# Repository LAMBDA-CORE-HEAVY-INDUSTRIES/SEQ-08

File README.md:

# SEQ-08

Desktop STM32F411 sequencer with eight CV outputs, eight gate outputs, clock I/O, and reset input.

- [Hardware design](doc/hw.md)
- [Bill of materials](doc/bom.md)
- [KiCad projects](pcb/README.md)
- [Firmware](fw/README.md)

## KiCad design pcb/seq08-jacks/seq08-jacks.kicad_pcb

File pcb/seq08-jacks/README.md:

# SEQ-08 jack board

This passive panel PCB holds nineteen PJ398SM jacks:

- J1-J8: CV outputs
- J9-J16: gate outputs
- J17: clock input
- J18: clock output
- J19: reset input
- J24-J25: keyed IDC connections to the main board

The clock and reset normal contacts connect to ground. Other normal contacts remain unconnected.

The provisional board is 160 x 100 mm with four 3.2 mm M3 mounting holes. Confirm the enclosure geometry before routing or ordering it.

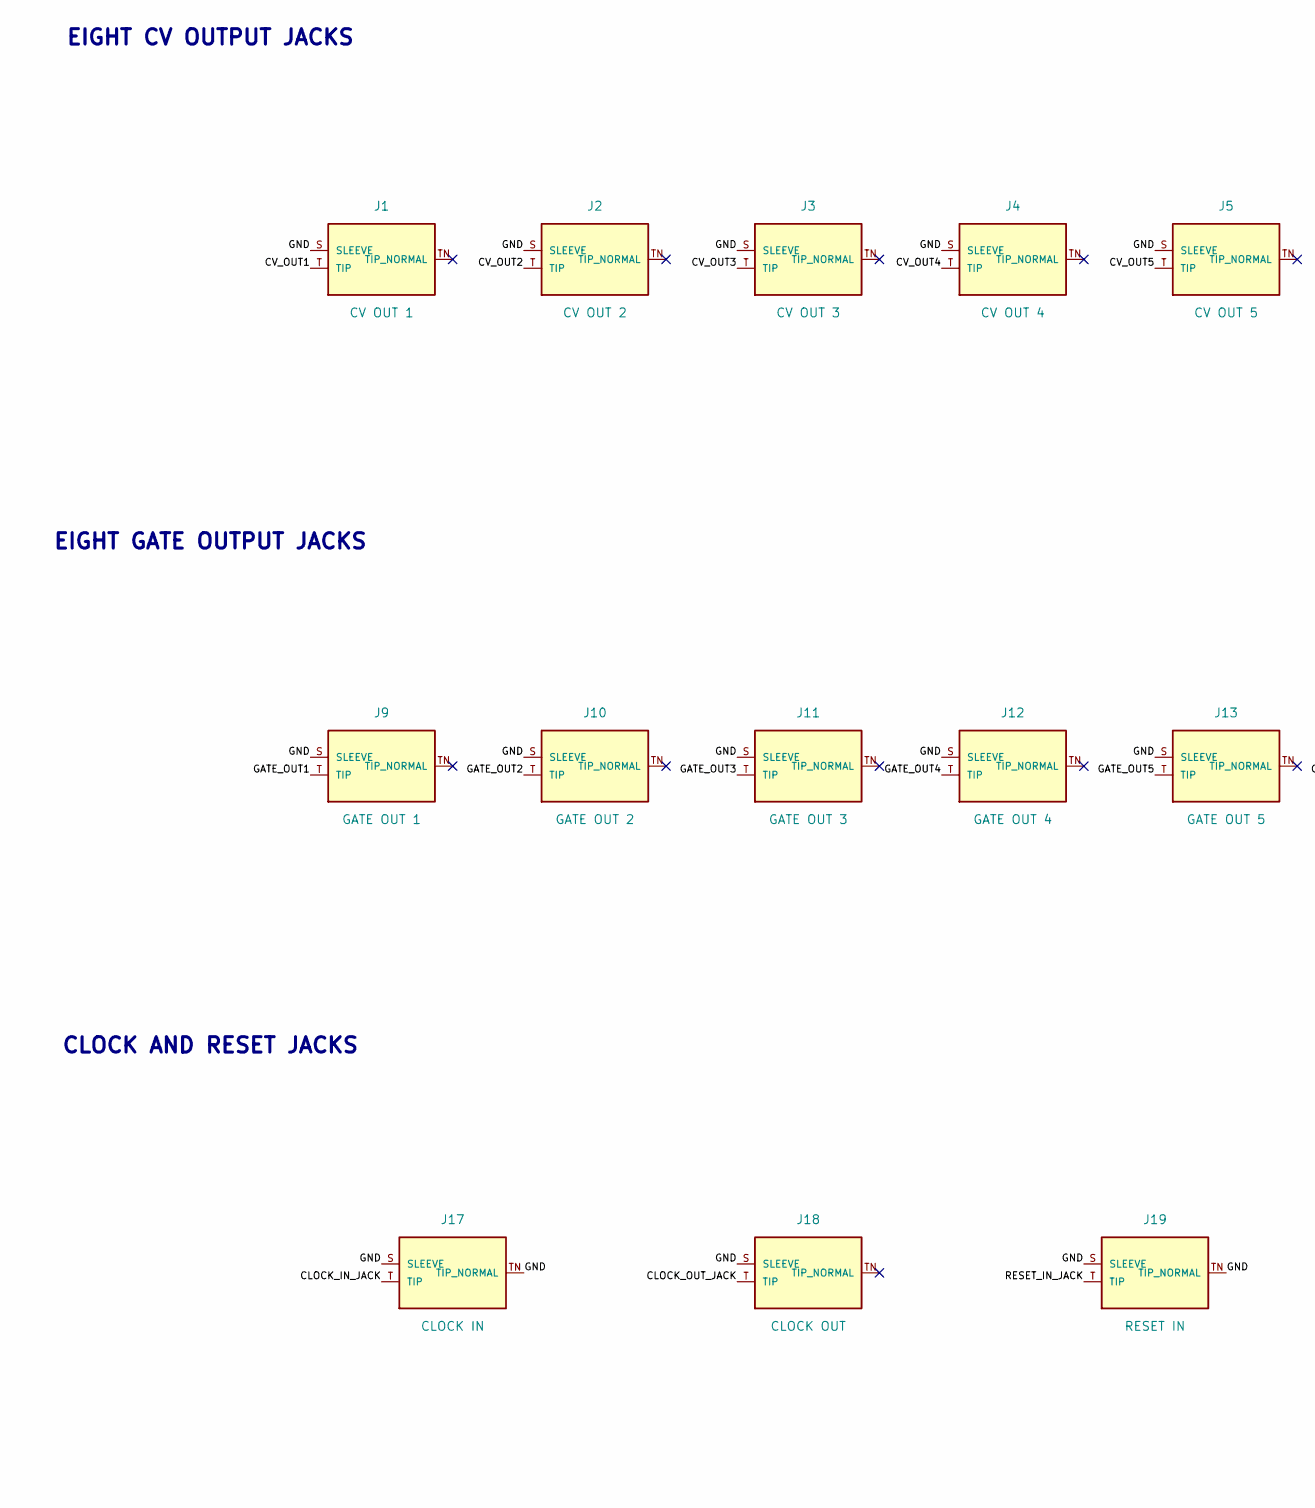
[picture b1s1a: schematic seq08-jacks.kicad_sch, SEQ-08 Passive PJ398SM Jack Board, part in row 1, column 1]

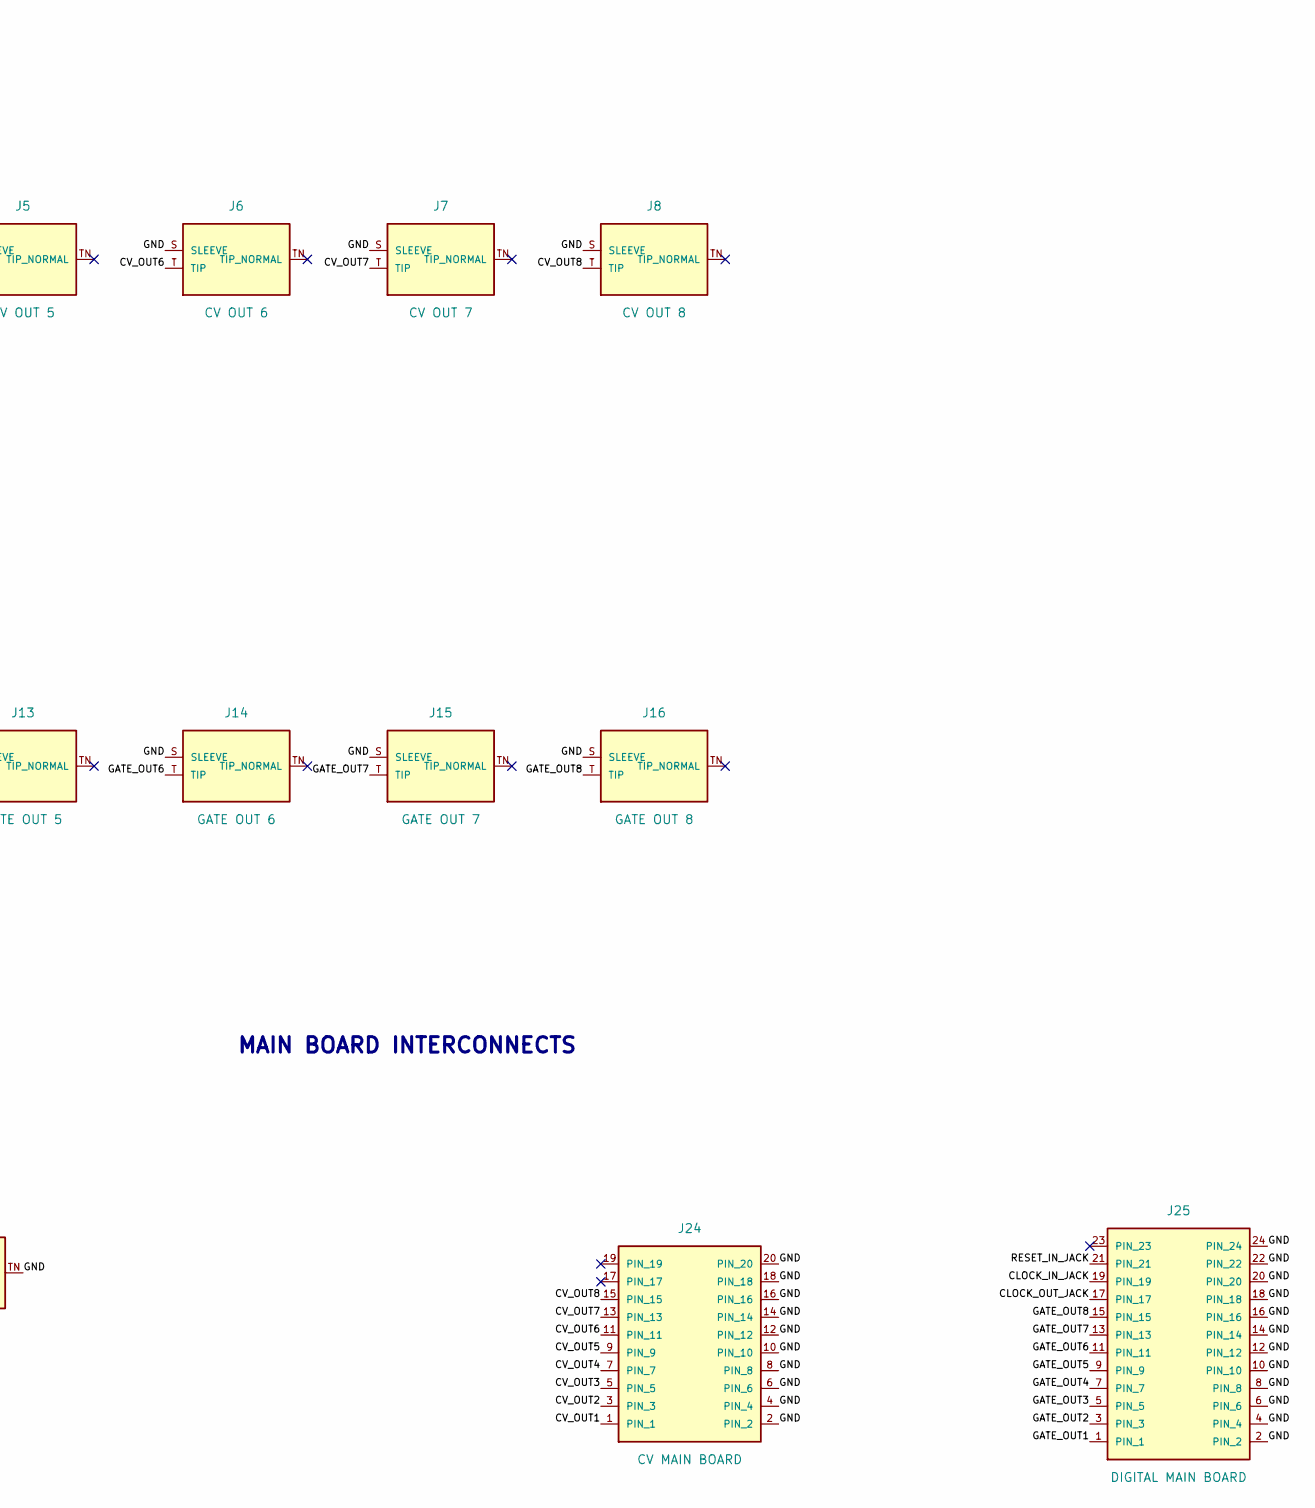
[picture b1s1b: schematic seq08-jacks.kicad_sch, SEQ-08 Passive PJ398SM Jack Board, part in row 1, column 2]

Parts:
J1: CV OUT 1; Jack_3.5mm_QingPu_WQP-PJ398SM_Vertical_CircularHoles
J2: CV OUT 2; Jack_3.5mm_QingPu_WQP-PJ398SM_Vertical_CircularHoles
J3: CV OUT 3; Jack_3.5mm_QingPu_WQP-PJ398SM_Vertical_CircularHoles
J4: CV OUT 4; Jack_3.5mm_QingPu_WQP-PJ398SM_Vertical_CircularHoles
J5: CV OUT 5; Jack_3.5mm_QingPu_WQP-PJ398SM_Vertical_CircularHoles
J6: CV OUT 6; Jack_3.5mm_QingPu_WQP-PJ398SM_Vertical_CircularHoles
J7: CV OUT 7; Jack_3.5mm_QingPu_WQP-PJ398SM_Vertical_CircularHoles
J8: CV OUT 8; Jack_3.5mm_QingPu_WQP-PJ398SM_Vertical_CircularHoles
J9: GATE OUT 1; Jack_3.5mm_QingPu_WQP-PJ398SM_Vertical_CircularHoles
J10: GATE OUT 2; Jack_3.5mm_QingPu_WQP-PJ398SM_Vertical_CircularHoles
J11: GATE OUT 3; Jack_3.5mm_QingPu_WQP-PJ398SM_Vertical_CircularHoles
J12: GATE OUT 4; Jack_3.5mm_QingPu_WQP-PJ398SM_Vertical_CircularHoles
J13: GATE OUT 5; Jack_3.5mm_QingPu_WQP-PJ398SM_Vertical_CircularHoles
J14: GATE OUT 6; Jack_3.5mm_QingPu_WQP-PJ398SM_Vertical_CircularHoles
J15: GATE OUT 7; Jack_3.5mm_QingPu_WQP-PJ398SM_Vertical_CircularHoles
J16: GATE OUT 8; Jack_3.5mm_QingPu_WQP-PJ398SM_Vertical_CircularHoles
J17: CLOCK IN; Jack_3.5mm_QingPu_WQP-PJ398SM_Vertical_CircularHoles
J18: CLOCK OUT; Jack_3.5mm_QingPu_WQP-PJ398SM_Vertical_CircularHoles
J19: RESET IN; Jack_3.5mm_QingPu_WQP-PJ398SM_Vertical_CircularHoles
J24: CV MAIN BOARD; IDC-Header_2x10_P2.54mm_Vertical
J25: DIGITAL MAIN BOARD; IDC-Header_2x12_P2.54mm_Vertical

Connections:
/CLOCK_IN_JACK: J17.T (TIP), J25.19 (PIN_19)
/CLOCK_OUT_JACK: J18.T (TIP), J25.17 (PIN_17)
/CV_OUT1: J1.T (TIP), J24.1 (PIN_1)
/CV_OUT2: J2.T (TIP), J24.3 (PIN_3)
/CV_OUT3: J3.T (TIP), J24.5 (PIN_5)
/CV_OUT4: J4.T (TIP), J24.7 (PIN_7)
/CV_OUT5: J5.T (TIP), J24.9 (PIN_9)
/CV_OUT6: J6.T (TIP), J24.11 (PIN_11)
/CV_OUT7: J7.T (TIP), J24.13 (PIN_13)
/CV_OUT8: J8.T (TIP), J24.15 (PIN_15)
/GATE_OUT1: J9.T (TIP), J25.1 (PIN_1)
/GATE_OUT2: J10.T (TIP), J25.3 (PIN_3)
/GATE_OUT3: J11.T (TIP), J25.5 (PIN_5)
/GATE_OUT4: J12.T (TIP), J25.7 (PIN_7)
/GATE_OUT5: J13.T (TIP), J25.9 (PIN_9)
/GATE_OUT6: J14.T (TIP), J25.11 (PIN_11)
/GATE_OUT7: J15.T (TIP), J25.13 (PIN_13)
/GATE_OUT8: J16.T (TIP), J25.15 (PIN_15)
/GND: J1.S (SLEEVE), J2.S (SLEEVE), J3.S (SLEEVE), J4.S (SLEEVE), J5.S (SLEEVE), J6.S (SLEEVE), J7.S (SLEEVE), J8.S (SLEEVE), J9.S (SLEEVE), J10.S (SLEEVE), J11.S (SLEEVE), J12.S (SLEEVE), J13.S (SLEEVE), J14.S (SLEEVE), J15.S (SLEEVE), J16.S (SLEEVE), J17.S (SLEEVE), J17.TN (TIP_NORMAL), J18.S (SLEEVE), J19.S (SLEEVE), J19.TN (TIP_NORMAL), J24.2 (PIN_2), J24.4 (PIN_4), J24.6 (PIN_6), J24.8 (PIN_8), J24.10 (PIN_10), J24.12 (PIN_12), J24.14 (PIN_14), J24.16 (PIN_16), J24.18 (PIN_18), J24.20 (PIN_20), J25.2 (PIN_2), J25.4 (PIN_4), J25.6 (PIN_6), J25.8 (PIN_8), J25.10 (PIN_10), J25.12 (PIN_12), J25.14 (PIN_14), J25.16 (PIN_16), J25.18 (PIN_18), J25.20 (PIN_20), J25.22 (PIN_22), J25.24 (PIN_24)
/RESET_IN_JACK: J19.T (TIP), J25.21 (PIN_21)

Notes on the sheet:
EIGHT CV OUTPUT JACKS
EIGHT GATE OUTPUT JACKS
CLOCK AND RESET JACKS
MAIN BOARD INTERCONNECTS

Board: 2 copper layers, 25 parts (0 on the bottom side), 20 nets, no tracks yet.

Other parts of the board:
H1, H2, H3, H4: M3 MOUNTING HOLE; MountingHole_3.2mm_M3

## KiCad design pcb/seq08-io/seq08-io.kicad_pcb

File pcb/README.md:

# PCB projects

Revision A uses two KiCad 10 projects:

- `seq08-io`: four-layer active main board
- `seq08-jacks`: two-layer passive board for nineteen PJ398SM jacks

See [`../doc/hw.md`](../doc/hw.md) for the electrical design and [`../doc/bom.md`](../doc/bom.md) for parts.

The display, DC jack, power switch, jacks, and buttons connect to the main board by cable. J24 and J25 connect the main board to the jack board.

## Regeneration

Edit the Python sources, then regenerate the KiCad schematics:

```sh
python3 pcb/seq08-io/generate_schematic.py
python3 pcb/seq08-jacks/generate_schematic.py
kicad-cli sch erc --exit-code-violations pcb/seq08-io/seq08-io.kicad_sch
kicad-cli sch erc --exit-code-violations pcb/seq08-jacks/seq08-jacks.kicad_sch
```

`populate_boards.py` creates the initial placement. It refuses to replace populated boards without `--replace`.

```sh
python3 pcb/populate_boards.py --replace seq08-io
python3 pcb/populate_boards.py --replace seq08-jacks
```

`--replace` discards PCB edits. Pass one project name to avoid replacing both boards.

## Current state

- Main board: 180 x 104 mm, 157 schematic footprints, four M3 mounting holes
- Jack board: 160 x 100 mm, 21 schematic footprints, four M3 mounting holes
- Schematics: ERC clean
- Placement: DRC clean
- Copper routing: not started

The display uses a keyed 2x20, 2.54 mm IDC header, 4-wire SPI, and 5 V power. Verify the physical module header before ordering a PCB.

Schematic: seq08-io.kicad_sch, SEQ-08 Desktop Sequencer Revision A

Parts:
C1: 100u/25V; C_Elec_8x10.2
C2: 22u/50V; C_Elec_6.3x7.7
C3: 470u/10V; C_Elec_8x10.2
C4, C20, C21, C33: 1u; C_0603_1608Metric
C5, C6, C22: 4.7u; C_0805_2012Metric
C7: 2.2u; C_0805_2012Metric
C8: 1u C0G; C_0805_2012Metric
C9, C10, C11, C12, C13, C14, C15, C16, C19, C32: 100n; C_0603_1608Metric
C17, C18: 1n C0G; C_0603_1608Metric
C23, C24, C25, C26: 100n MCU VDD; C_0603_1608Metric
C27: 100n VBAT; C_0603_1608Metric
C28: 100n VDDA; C_0603_1608Metric
C29: 1u VDDA; C_0603_1608Metric
C30: 4.7u VCAP; C_0805_2012Metric
C31: 100n NRST; C_0603_1608Metric
D1: SS34; D_SMA
D2: SMBJ15A; D_SMB
D3, D4, D5, D6: BAT54; D_SOD-323
J20: SWITCHED 12V CASE HARNESS; Molex_Micro-Fit_3.0_43650-0200_1x02_P3.00mm_Horizontal
J23: ER-TFT070A2-6-5633 HEADER; IDC-Header_2x20_P2.54mm_Vertical
J24: CV JACK BOARD; IDC-Header_2x10_P2.54mm_Vertical
J25: GATE CLOCK RESET JACK BOARD; IDC-Header_2x12_P2.54mm_Vertical
J26: STEP BUTTON BOARD 16; JST_XH_B8B-XH-A_1x08_P2.50mm_Vertical
J27: CORTEX SWD 10-PIN; PinHeader_2x05_P1.27mm_Vertical
J28: CHANNEL BUTTON BOARD 8; JST_XH_B8B-XH-A_1x08_P2.50mm_Vertical
J29: CONTROL BUTTON BOARD 15+; JST_XH_B8B-XH-A_1x08_P2.50mm_Vertical
R1: PTC 1.1A; Fuse_1206_3216Metric
R2, R3: FB 600R@100MHz; L_1206_3216Metric
R4: 856k 1%; R_0603_1608Metric
R5: 500k 1%; R_0603_1608Metric
R6, R7, R8, R72, R73, R74, R75, R77, R78, R79, R80, R82, R83, R84, R85: 33R; R_0603_1608Metric
R9, R13, R59, R63, R65, R66, R67, R87: 10k; R_0603_1608Metric
R10, R11, R12, R38, R40, R42, R44, R46, R48, R50, R52, R54, R56, R60, R69, R70, R71, R88, R89: 100k; R_0603_1608Metric
R14, R15, R17, R18, R20, R21, R23, R24, R26, R27, R29, R30, R32, R33, R35, R36: 10k 0.05%; R_0603_1608Metric
R16, R19, R22, R25, R28, R31, R34, R37: 1k 0.1%; R_0805_2012Metric
R39, R41, R43, R45, R47, R49, R51, R53, R55: 1k; R_0805_2012Metric
R57, R61: 33k; R_0603_1608Metric
R58, R62: 1M; R_0603_1608Metric
R64: 49.9k; R_0603_1608Metric
R68: FB 600R@100MHz; L_0603_1608Metric
R76, R81, R86: 100R; R_0603_1608Metric
SW2: RESET; SW_SPST_EVQPE1
SW3: BOOT0; SW_SPST_EVQPE1
TP1: CV1_RAW; TestPoint_Loop_D2.50mm_Drill1.0mm
TP2: CV2_RAW; TestPoint_Loop_D2.50mm_Drill1.0mm
TP3: CV3_RAW; TestPoint_Loop_D2.50mm_Drill1.0mm
TP4: CV4_RAW; TestPoint_Loop_D2.50mm_Drill1.0mm
TP5: CV5_RAW; TestPoint_Loop_D2.50mm_Drill1.0mm
TP6: CV6_RAW; TestPoint_Loop_D2.50mm_Drill1.0mm
TP7: CV7_RAW; TestPoint_Loop_D2.50mm_Drill1.0mm
TP8: CV8_RAW; TestPoint_Loop_D2.50mm_Drill1.0mm
U1: DAC8568ICPW; TSSOP-16_4.4x5mm_P0.65mm
U2, U3: OPA4197ID; SOIC-14_3.9x8.7mm_P1.27mm
U4, U5: 74AHCT244D; SOIC-20W_7.5x12.8mm_P1.27mm
U6: LM393BIDR; SOIC-8_3.9x4.9mm_P1.27mm
U7: TSR 2-2450N; Converter_DCDC_TRACO_TSR2-24xxN_TSR2-24xxxN_THT
U8: LM27761DSGR; Texas_DSG0008A_WSON-8-1EP_2x2mm_P0.5mm_EP0.9x1.6mm_ThermalV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
U9: STM32F411RET6; LQFP-64_10x10mm_P0.5mm
U10: TLV75533PDBVR; SOT-23-5
U11: CY15B104QN-50SXI; SOIC-8_5.3x5.3mm_P1.27mm

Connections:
/12V_FUSED: D1.1 (A), R1.2
/12V_SW: J20.1 (PIN_1), R1.1
/+3V3: C21.1 (+), C22.1 (+), C23.1 (+), C24.1 (+), C25.1 (+), C26.1 (+), C27.1 (+), C32.1 (+), C33.1 (+), D3.2 (K), D5.2 (K), J26.2 (PIN_2), J27.1 (PIN_1), J28.2 (PIN_2), J29.2 (PIN_2), R9.1, R13.1, R59.1, R63.1, R64.1, R66.1, R68.1, R87.1, SW3.1 (IN), U9.1 (VBAT), U9.19 (VDD), U9.32 (VDD), U9.48 (VDD), U9.64 (VDD), U10.5 (OUT), U11.3 (/WP), U11.7 (DNU), U11.8 (VDD)
/+3V3_MCU_A: C28.1 (+), C29.1 (+), R68.2, U9.13 (VDDA/VREF+)
/+5V: C5.1 (+), C10.1 (+), C15.1 (+), C16.1 (+), C20.1 (+), J26.1 (PIN_1), J28.1 (PIN_1), J29.1 (PIN_1), R2.1, R3.1, U4.20 (VCC), U5.20 (VCC), U6.8 (VCC), U7.3 (VOUT), U8.2 (VIN), U8.5 (EN), U10.1 (IN), U10.3 (EN)
/+5V_ANALOG: C9.1 (+), R3.2, U1.3 (AVDD), U1.9 (CLR)
/+5V_DISPLAY: C3.1 (+), J23.3 (VDD), J23.4 (VDD), J23.37 (VDD), J23.38 (VDD), R2.2
/+12V_A: C1.1 (+), C2.1 (+), C11.1 (+), C13.1 (+), D1.2 (K), D2.1 (A), U2.4 (V+), U3.4 (V+), U7.1 (VIN)
/-3V3_A: C7.1 (+), C12.1 (+), C14.1 (+), R4.1, U2.11 (V-), U3.11 (V-), U8.6 (VOUT)
/BOOT0: R67.1, SW3.2 (OUT), U9.60 (BOOT0)
/BUTTON_CLK_MCU: R11.1, R72.1, R77.1, R82.1, U9.61 (PB8)
/BUTTON_FRAME_MCU: R12.1, R73.1, R78.1, R83.1, U9.62 (PB9)
/CHANNEL_BUTTON_CLK: J28.4 (PIN_4), R77.2
/CHANNEL_BUTTON_DATA: J28.8 (PIN_8), R81.1
/CHANNEL_BUTTON_DATA_MCU: R81.2, U9.15 (PA1)
/CHANNEL_BUTTON_FRAME: J28.5 (PIN_5), R78.2
/CHANNEL_LED_BLANK: J28.6 (PIN_6), R79.2
/CHANNEL_LED_DATA: J28.7 (PIN_7), R80.2
/CHANNEL_LED_DATA_MCU: R70.1, R80.1, U9.14 (PA0)
/CLOCK_IN_JACK: J25.19 (PIN_19), R56.1
/CLOCK_IN_LOGIC: R58.1, R59.2, U6.1 (OUT1), U9.40 (PC9)
/CLOCK_OUT_5V: R55.1, U5.3 (2Y0)
/CLOCK_OUT_JACK: J25.17 (PIN_17), R55.2
/CLOCK_OUT_MCU: R54.1, U5.17 (2A0), U9.39 (PC8)
/CLOCK_SENSE: C17.1 (+), D3.1 (A), D4.2 (K), R56.2, R57.1, R58.2, U6.3 (1+)
/CONTROL_BUTTON_CLK: J29.4 (PIN_4), R82.2
/CONTROL_BUTTON_DATA: J29.8 (PIN_8), R86.1
/CONTROL_BUTTON_DATA_MCU: R86.2, U9.17 (PA3)
/CONTROL_BUTTON_FRAME: J29.5 (PIN_5), R83.2
/CONTROL_LED_BLANK: J29.6 (PIN_6), R84.2
/CONTROL_LED_DATA: J29.7 (PIN_7), R85.2
/CONTROL_LED_DATA_MCU: R71.1, R85.1, U9.16 (PA2)
/CV_FB1: R14.2, R15.1, U2.2 (A-)
/CV_FB2: R17.2, R18.1, U2.6 (B-)
/CV_FB3: R20.2, R21.1, U2.9 (C-)
/CV_FB4: R23.2, R24.1, U2.13 (D-)
/CV_FB5: R26.2, R27.1, U3.2 (A-)
/CV_FB6: R29.2, R30.1, U3.6 (B-)
/CV_FB7: R32.2, R33.1, U3.9 (C-)
/CV_FB8: R35.2, R36.1, U3.13 (D-)
/CV_OUT1: J24.1 (PIN_1), R16.2
/CV_OUT2: J24.3 (PIN_3), R19.2
/CV_OUT3: J24.5 (PIN_5), R22.2
/CV_OUT4: J24.7 (PIN_7), R25.2
/CV_OUT5: J24.9 (PIN_9), R28.2
/CV_OUT6: J24.11 (PIN_11), R31.2
/CV_OUT7: J24.13 (PIN_13), R34.2
/CV_OUT8: J24.15 (PIN_15), R37.2
/CV_RAW1: R14.1, R16.1, TP1.1, U2.1 (OUTA)
/CV_RAW2: R17.1, R19.1, TP2.1, U2.7 (OUTB)
/CV_RAW3: R20.1, R22.1, TP3.1, U2.8 (OUTC)
/CV_RAW4: R23.1, R25.1, TP4.1, U2.14 (OUTD)
/CV_RAW5: R26.1, R28.1, TP5.1, U3.1 (OUTA)
/CV_RAW6: R29.1, R31.1, TP6.1, U3.7 (OUTB)
/CV_RAW7: R32.1, R34.1, TP7.1, U3.8 (OUTC)
/CV_RAW8: R35.1, R37.1, TP8.1, U3.14 (OUTD)
/DAC_LDAC_5V: U1.1 (LDAC), U5.12 (1Y3)
/DAC_LDAC_MCU: U5.8 (1A3), U9.35 (PB14)
/DAC_MOSI_5V: U1.15 (DIN), U5.16 (1Y1)
/DAC_MOSI_MCU: U5.4 (1A1), U9.36 (PB15)
/DAC_OUT1: U1.4 (VOUTA), U2.3 (A+)
/DAC_OUT2: U1.13 (VOUTB), U2.5 (B+)
/DAC_OUT3: U1.5 (VOUTC), U2.10 (C+)
/DAC_OUT4: U1.12 (VOUTD), U2.12 (D+)
/DAC_OUT5: U1.6 (VOUTE), U3.3 (A+)
/DAC_OUT6: U1.11 (VOUTF), U3.5 (B+)
/DAC_OUT7: U1.7 (VOUTG), U3.10 (C+)
/DAC_OUT8: U1.10 (VOUTH), U3.12 (D+)
/DAC_SCLK_5V: U1.16 (SCLK), U5.18 (1Y0)
/DAC_SCLK_MCU: U5.2 (1A0), U9.34 (PB13)
/DAC_SYNC_5V: U1.2 (SYNC), U5.14 (1Y2)
/DAC_SYNC_MCU: U5.6 (1A2), U9.33 (PB12)
/DAC_VREF: C8.1 (+), U1.8 (VREF)
/DISPLAY_BACKLIGHT: J23.14 (BL_CONTROL), R10.1, U9.29 (PB10)
/DISPLAY_CS: J23.5 (/SCS), R6.2
/DISPLAY_MISO: J23.6 (SDO), U9.22 (PA6)
/DISPLAY_MOSI: J23.7 (SDI), R8.2
/DISPLAY_RESET: J23.11 (/RESET), R9.2, U9.26 (PB0)
/DISPLAY_SCK: J23.8 (SCLK), R7.2
/DISP_CS_MCU: R6.1, U9.20 (PA4)
/DISP_MOSI_MCU: R8.1, U9.23 (PA7)
/DISP_SCK_MCU: R7.1, U9.21 (PA5)
/FRAM_CS: R87.2, U9.58 (PB6), U11.1 (/CS)
/FRAM_MISO: U9.52 (PC11), U11.2 (SO)
/FRAM_MOSI: R89.1, U9.53 (PC12), U11.5 (SI)
/FRAM_SCK: R88.1, U9.51 (PC10), U11.6 (SCK)
/GATE1_5V: R39.1, U4.18 (1Y0)
/GATE1_MCU: R38.1, U4.2 (1A0), U9.8 (PC0)
/GATE2_5V: R41.1, U4.16 (1Y1)
/GATE2_MCU: R40.1, U4.4 (1A1), U9.9 (PC1)
/GATE3_5V: R43.1, U4.14 (1Y2)
/GATE3_MCU: R42.1, U4.6 (1A2), U9.10 (PC2)
/GATE4_5V: R45.1, U4.12 (1Y3)
/GATE4_MCU: R44.1, U4.8 (1A3), U9.11 (PC3)
/GATE5_5V: R47.1, U4.3 (2Y0)
/GATE5_MCU: R46.1, U4.17 (2A0), U9.24 (PC4)
/GATE6_5V: R49.1, U4.5 (2Y1)
/GATE6_MCU: R48.1, U4.15 (2A1), U9.25 (PC5)
/GATE7_5V: R51.1, U4.7 (2Y2)
/GATE7_MCU: R50.1, U4.13 (2A2), U9.37 (PC6)
/GATE8_5V: R53.1, U4.9 (2Y3)
/GATE8_MCU: R52.1, U4.11 (2A3), U9.38 (PC7)
/GATE_OUT1: J25.1 (PIN_1), R39.2
/GATE_OUT2: J25.3 (PIN_3), R41.2
/GATE_OUT3: J25.5 (PIN_5), R43.2
/GATE_OUT4: J25.7 (PIN_7), R45.2
/GATE_OUT5: J25.9 (PIN_9), R47.2
/GATE_OUT6: J25.11 (PIN_11), R49.2
/GATE_OUT7: J25.13 (PIN_13), R51.2
/GATE_OUT8: J25.15 (PIN_15), R53.2
/GND: C1.2 (-), C2.2 (-), C3.2 (-), C5.2 (-), C6.2 (-), C7.2 (-), C8.2 (-), C9.2 (-), C10.2 (-), C11.2 (-), C12.2 (-), C13.2 (-), C14.2 (-), C15.2 (-), C16.2 (-), C17.2 (-), C18.2 (-), C19.2 (-), C20.2 (-), C21.2 (-), C22.2 (-), C23.2 (-), C24.2 (-), C25.2 (-), C26.2 (-), C27.2 (-), C28.2 (-), C29.2 (-), C30.2 (-), C31.2 (-), C32.2 (-), C33.2 (-), D2.2 (K), D4.1 (A), D6.1 (A), J20.2 (PIN_2), J23.1 (VSS), J23.2 (VSS), J23.13 (VSS), J23.31 (VSS), J23.39 (VSS), J23.40 (VSS), J24.2 (PIN_2), J24.4 (PIN_4), J24.6 (PIN_6), J24.8 (PIN_8), J24.10 (PIN_10), J24.12 (PIN_12), J24.14 (PIN_14), J24.16 (PIN_16), J24.18 (PIN_18), J24.20 (PIN_20), J25.2 (PIN_2), J25.4 (PIN_4), J25.6 (PIN_6), J25.8 (PIN_8), J25.10 (PIN_10), J25.12 (PIN_12), J25.14 (PIN_14), J25.16 (PIN_16), J25.18 (PIN_18), J25.20 (PIN_20), J25.22 (PIN_22), J25.24 (PIN_24), J26.3 (PIN_3), J27.3 (PIN_3), J27.5 (PIN_5), J27.9 (PIN_9), J28.3 (PIN_3), J29.3 (PIN_3), R5.2, R10.2, R11.2, R12.2, R15.2, R18.2, R21.2, R24.2, R27.2, R30.2, R33.2, R36.2, R38.2, R40.2, R42.2, R44.2, R46.2, R48.2, R50.2, R52.2, R54.2, R57.2, R61.2, R65.2, R67.2, R69.2, R70.2, R71.2, R88.2, R89.2, SW2.2 (OUT), U1.14 (0V), U4.1 (1OE), U4.10 (0V), U4.19 (2OE), U5.1 (1OE), U5.10 (0V), U5.11 (2A3), U5.13 (2A2), U5.15 (2A1), U5.19 (2OE), U6.4 (0V), U7.2 (0V), U8.4 (0V), U9.12 (VSSA/VREF-), U9.18 (VSS), U9.31 (VSS), U9.47 (VSS), U9.63 (VSS), U10.2 (GND), U11.4 (VSS)
/LED_BLANK_MCU: R13.2, R74.1, R79.1, R84.1, U9.41 (PA8)
/LM_C1N: C4.2 (-), U8.3 (C1-)
/LM_C1P: C4.1 (+), U8.1 (C1+)
/LM_CPOUT: C6.1 (+), U8.8 (CPOUT)
/LM_FB: R4.2, R5.1, U8.7 (VFB)
/MCU_NRST: C31.1 (+), J27.10 (PIN_10), R66.2, SW2.1 (IN), U9.7 (NRST)
/MCU_VCAP: C30.1 (+), U9.30 (VCAP_1)
/RESET_IN_JACK: J25.21 (PIN_21), R60.1
/RESET_IN_LOGIC: R62.1, R63.2, U6.7 (OUT2), U9.43 (PA10)
/RESET_SENSE: C18.1 (+), D5.1 (A), D6.2 (K), R60.2, R61.1, R62.2, U6.5 (2+)
/STEP_BUTTON_CLK: J26.4 (PIN_4), R72.2
/STEP_BUTTON_DATA: J26.8 (PIN_8), R76.1
/STEP_BUTTON_DATA_MCU: R76.2, U9.28 (PB2)
/STEP_BUTTON_FRAME: J26.5 (PIN_5), R73.2
/STEP_LED_BLANK: J26.6 (PIN_6), R74.2
/STEP_LED_DATA: J26.7 (PIN_7), R75.2
/STEP_LED_DATA_MCU: R69.1, R75.1, U9.27 (PB1)
/SWCLK: J27.4 (PIN_4), U9.49 (PA14/SWCLK)
/SWDIO: J27.2 (PIN_2), U9.46 (PA13/SWDIO)
/SWO: J27.6 (PIN_6), U9.55 (PB3/SWO)
/SYNC_REF: C19.1 (+), R64.2, R65.1, U6.2 (1-), U6.6 (2-)

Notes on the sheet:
POWER INPUT AND RAILS
STM32 AND DISPLAY
F-RAM PRESET STORAGE
DAC AND 0-10V CV OUTPUTS
GATE AND CLOCK OUTPUTS
CLOCK AND RESET INPUTS
PASSIVE JACK BOARD INTERCONNECTS

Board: 4 copper layers, 161 parts (0 on the bottom side), 132 nets, no tracks yet.

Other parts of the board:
H1, H2, H3, H4: M3 MOUNTING HOLE; MountingHole_3.2mm_M3

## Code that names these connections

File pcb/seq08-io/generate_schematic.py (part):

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
mcu_pin_names = {
    1: "VBAT", 2: "PC13", 3: "PC14/OSC32_IN", 4: "PC15/OSC32_OUT",
    5: "PH0/OSC_IN", 6: "PH1/OSC_OUT", 7: "NRST", 8: "PC0", 9: "PC1",
    10: "PC2", 11: "PC3", 12: "VSSA/VREF-", 13: "VDDA/VREF+", 14: "PA0",
    15: "PA1", 16: "PA2", 17: "PA3", 18: "VSS", 19: "VDD", 20: "PA4",
    21: "PA5", 22: "PA6", 23: "PA7", 24: "PC4", 25: "PC5", 26: "PB0",
    27: "PB1", 28: "PB2", 29: "PB10", 30: "VCAP_1", 31: "VSS", 32: "VDD",
    33: "PB12", 34: "PB13", 35: "PB14", 36: "PB15", 37: "PC6", 38: "PC7",
    39: "PC8", 40: "PC9", 41: "PA8", 42: "PA9", 43: "PA10", 44: "PA11",
    45: "PA12", 46: "PA13/SWDIO", 47: "VSS", 48: "VDD", 49: "PA14/SWCLK",
    50: "PA15", 51: "PC10", 52: "PC11", 53: "PC12", 54: "PD2", 55: "PB3/SWO",
    56: "PB4", 57: "PB5", 58: "PB6", 59: "PB7", 60: "BOOT0", 61: "PB8",
    62: "PB9", 63: "VSS", 64: "VDD",
}
mcu_power_pins = {1, 12, 13, 18, 19, 31, 32, 47, 48, 63, 64}
mcu_pins = []
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    "1": "LM_C1P", "2": "+5V", "3": "LM_C1N", "4": "GND", "5": "+5V",
    "6": "-3V3_A", "7": "LM_FB", "8": "LM_CPOUT",
}, "Package_SON:Texas_DSG0008A_WSON-8-1EP_2x2mm_P0.5mm_EP0.9x1.6mm_ThermalVias")
add_two_pin("C", "C", "1u", 105, 106, "LM_C1P", "LM_C1N", "Capacitor_SMD:C_0603_1608Metric")
add_two_pin("C", "C", "4.7u", 105, 117, "+5V", "GND", "Capacitor_SMD:C_0805_2012Metric")
add_two_pin("C", "C", "4.7u", 105, 128, "LM_CPOUT", "GND", "Capacitor_SMD:C_0805_2012Metric")
add_two_pin("C", "C", "2.2u", 105, 139, "-3V3_A", "GND", "Capacitor_SMD:C_0805_2012Metric")
add_two_pin("R", "R", "856k 1%", 135, 112, "-3V3_A", "LM_FB", "Resistor_SMD:R_0603_1608Metric")
add_two_pin("R", "R", "500k 1%", 135, 123, "LM_FB", "GND", "Resistor_SMD:R_0603_1608Metric")


add_section("STM32 AND DISPLAY", 170, 15)
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    "Package_QFP:LQFP-64_10x10mm_P0.5mm",
    "https://www.st.com/resource/en/datasheet/stm32f411re.pdf",
)
add_two_pin("R", "R", "33R", 275, 32, "DISP_CS_MCU", "DISPLAY_CS", "Resistor_SMD:R_0603_1608Metric")
add_two_pin("R", "R", "33R", 275, 43, "DISP_SCK_MCU", "DISPLAY_SCK", "Resistor_SMD:R_0603_1608Metric")
add_two_pin("R", "R", "33R", 275, 54, "DISP_MOSI_MCU", "DISPLAY_MOSI", "Resistor_SMD:R_0603_1608Metric")
add_two_pin("R", "R", "10k", 275, 65, "+3V3", "DISPLAY_RESET", "Resistor_SMD:R_0603_1608Metric")
add_two_pin("R", "R", "100k", 275, 76, "DISPLAY_BACKLIGHT", "GND", "Resistor_SMD:R_0603_1608Metric")
add_two_pin("R", "R", "100k", 275, 87, "BUTTON_CLK_MCU", "GND", "Resistor_SMD:R_0603_1608Metric")
add_two_pin("R", "R", "100k", 275, 98, "BUTTON_FRAME_MCU", "GND", "Resistor_SMD:R_0603_1608Metric")
add_two_pin("R", "R", "10k", 275, 109, "+3V3", "LED_BLANK_MCU", "Resistor_SMD:R_0603_1608Metric")
add_component("R", "R69", "100k", 275, 120, {"1": "STEP_LED_DATA_MCU", "2": "GND"}, "Resistor_SMD:R_0603_1608Metric")
add_component("R", "R70", "100k", 275, 131, {"1": "CHANNEL_LED_DATA_MCU", "2": "GND"}, "Resistor_SMD:R_0603_1608Metric")
add_component("R", "R71", "100k", 275, 142, {"1": "CONTROL_LED_DATA_MCU", "2": "GND"}, "Resistor_SMD:R_0603_1608Metric")
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    "10": "DAC_OUT8", "11": "DAC_OUT6", "12": "DAC_OUT4", "13": "DAC_OUT2", "14": "GND",
    "15": "DAC_MOSI_5V", "16": "DAC_SCLK_5V",
}, "Package_SO:TSSOP-16_4.4x5mm_P0.65mm", "https://www.ti.com/lit/ds/symlink/dac8568.pdf")
add_two_pin("C", "C", "1u C0G", 120, 190, "DAC_VREF", "GND", "Capacitor_SMD:C_0805_2012Metric")
add_two_pin("C", "C", "100n", 120, 201, "+5V_ANALOG", "GND", "Capacitor_SMD:C_0603_1608Metric")

add_component("74AHCT244", "U5", "74AHCT244D", 70, 285, {
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    y = 83 + (channel - 1) * 12
    add_two_pin("R", "R", "100k", 625, y, f"GATE{channel}_MCU", "GND", "Resistor_SMD:R_0603_1608Metric")
    add_two_pin("R", "R", "1k", 675, y, f"GATE{channel}_5V", f"GATE_OUT{channel}", "Resistor_SMD:R_0805_2012Metric")
add_two_pin("R", "R", "100k", 625, 181, "CLOCK_OUT_MCU", "GND", "Resistor_SMD:R_0603_1608Metric")
add_two_pin("R", "R", "1k", 675, 181, "CLOCK_OUT_5V", "CLOCK_OUT_JACK", "Resistor_SMD:R_0805_2012Metric")


add_section("CLOCK AND RESET INPUTS", 600, 215)
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    add_two_pin("R", "R", "1M", x + 35, y + 20, output_net, sense_net, "Resistor_SMD:R_0603_1608Metric")
    add_two_pin("R", "R", "10k", x + 70, y, "+3V3", output_net, "Resistor_SMD:R_0603_1608Metric")

add_two_pin("R", "R", "49.9k", 660, 370, "+3V3", "SYNC_REF", "Resistor_SMD:R_0603_1608Metric")
add_two_pin("R", "R", "10k", 705, 370, "SYNC_REF", "GND", "Resistor_SMD:R_0603_1608Metric")
add_two_pin("C", "C", "100n", 750, 370, "SYNC_REF", "GND", "Capacitor_SMD:C_0603_1608Metric")


add_section("PASSIVE JACK BOARD INTERCONNECTS", 600, 405)
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
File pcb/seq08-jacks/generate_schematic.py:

#!/usr/bin/env python3

from pathlib import Path
from uuid import NAMESPACE_URL, uuid5


PROJECT = "seq08-jacks"
ROOT_UUID = str(uuid5(NAMESPACE_URL, f"{PROJECT}/root"))
ROOT = Path(__file__).parent
SCHEMATIC_OUTPUT = ROOT / f"{PROJECT}.kicad_sch"
SYMBOL_LIBRARY_OUTPUT = ROOT / "seq08-jacks.kicad_sym"
PJ398SM_FOOTPRINT = "Connector_Audio:Jack_3.5mm_QingPu_WQP-PJ398SM_Vertical_CircularHoles"


def uid(*parts):
    return str(uuid5(NAMESPACE_URL, "/".join((PROJECT, *map(str, parts)))))


def effects(size=1.27, justify=None, hide=False, bold=False):
    justify_text = f"\n\t\t\t\t(justify {justify})" if justify else ""
    hide_text = "\n\t\t\t\t(hide yes)" if hide else ""
    bold_text = "\n\t\t\t\t(bold yes)" if bold else ""
    return f"""(effects
\t\t\t(font
\t\t\t\t(size {size} {size}){bold_text}
\t\t\t){justify_text}{hide_text}
\t\t)"""


symbols = {}
components = []
labels = []
no_connects = []
texts = []


def define_symbol(name, pins, width, height):
    left = [pin for pin in pins if pin[3] == "left"]
    right = [pin for pin in pins if pin[3] == "right"]
    placed_pins = []
    for side, side_pins in (("left", left), ("right", right)):
        start = -((len(side_pins) - 1) * 2.54) / 2
        for index, (number, pin_name, pin_type, _) in enumerate(side_pins):
            x = -width / 2 - 2.54 if side == "left" else width / 2 + 2.54
            y = start + index * 2.54
            rotation = 0 if side == "left" else 180
            placed_pins.append((number, pin_name, pin_type, side, x, y, rotation))
    symbols[name] = {"width": width, "height": height, "pins": placed_pins}


def symbol_definition(name, symbol, qualified=True):
    library_name = f"SEQ08_JACKS:{name}" if qualified else name
    pin_text = []
    for number, pin_name, pin_type, _, x, y, rotation in symbol["pins"]:
        pin_text.append(f"""\t\t\t(pin {pin_type} line
\t\t\t\t(at {x:.3f} {y:.3f} {rotation})
\t\t\t\t(length 2.54)
\t\t\t\t(name "{pin_name}" {effects(1.0)})
\t\t\t\t(number "{number}" {effects(1.0)})
\t\t\t)""")
    half_width = symbol["width"] / 2
    half_height = symbol["height"] / 2
    return f"""\t\t(symbol "{library_name}"
\t\t\t(pin_names (offset 1.0))
\t\t\t(exclude_from_sim no)
\t\t\t(in_bom yes)
\t\t\t(on_board yes)
\t\t\t(property "Reference" "J" (at 0 {-half_height - 2.54:.3f} 0) {effects(1.27)})
\t\t\t(property "Value" "{name}" (at 0 {half_height + 2.54:.3f} 0) {effects(1.27)})
\t\t\t(property "Footprint" "" (at 0 0 0) {effects(1.0, hide=True)})
\t\t\t(property "Datasheet" "" (at 0 0 0) {effects(1.0, hide=True)})
\t\t\t(property "Description" "" (at 0 0 0) {effects(1.0, hide=True)})
\t\t\t(symbol "{name}_0_1"
\t\t\t\t(rectangle
\t\t\t\t\t(start {-half_width:.3f} {-half_height:.3f})
\t\t\t\t\t(end {half_width:.3f} {half_height:.3f})
\t\t\t\t\t(stroke (width 0.254) (type solid))
\t\t\t\t\t(fill (type background))
\t\t\t\t)
\t\t\t)
\t\t\t(symbol "{name}_1_1"
{chr(10).join(pin_text)}
\t\t\t)
\t\t\t(embedded_fonts no)
\t\t)"""


def add_label(net, x, y, side, key):
    rotation = 180 if side == "left" else 0
    justification = "right bottom" if side == "left" else "left bottom"
    labels.append(f"""\t(label "{net}"
\t\t(at {x:.3f} {y:.3f} {rotation})
\t\t{effects(1.0, justify=justification)}
\t\t(uuid "{uid('label', key, net)}")
\t)""")


def add_component(symbol_name, reference, value, x, y, pin_nets, footprint):
    x = round(x / 1.27) * 1.27
    y = round(y / 1.27) * 1.27
    symbol = symbols[symbol_name]
    pin_instances = []
    for number, _, _, side, pin_x, pin_y, _ in symbol["pins"]:
        absolute_x = x + pin_x
        absolute_y = y - pin_y
        net = pin_nets.get(number)
        pin_instances.append(f"\t\t(pin \"{number}\" (uuid \"{uid('pin', reference, number)}\"))")
        if net:
            add_label(net, absolute_x, absolute_y, side, f"{reference}-{number}")
        else:
            no_connects.append(f"""\t(no_connect
\t\t(at {absolute_x:.3f} {absolute_y:.3f})
\t\t(uuid "{uid('nc', reference, number)}")
\t)""")
    components.append(f"""\t(symbol
\t\t(lib_id "SEQ08_JACKS:{symbol_name}")
\t\t(at {x:.3f} {y:.3f} 0)
\t\t(unit 1)
\t\t(exclude_from_sim no)
\t\t(in_bom yes)
\t\t(on_board yes)
\t\t(dnp no)
\t\t(uuid "{uid('component', reference)}")
\t\t(property "Reference" "{reference}" (at {x:.3f} {y - symbol['height'] / 2 - 2.54:.3f} 0) {effects(1.27)})
\t\t(property "Value" "{value}" (at {x:.3f} {y + symbol['height'] / 2 + 2.54:.3f} 0) {effects(1.27)})
\t\t(property "Footprint" "{footprint}" (at {x:.3f} {y:.3f} 0) {effects(1.0, hide=True)})
\t\t(property "Datasheet" "" (at {x:.3f} {y:.3f} 0) {effects(1.0, hide=True)})
\t\t(property "Description" "" (at {x:.3f} {y:.3f} 0) {effects(1.0, hide=True)})
{chr(10).join(pin_instances)}
\t\t(instances
\t\t\t(project "{PROJECT}"
\t\t\t\t(path "/{ROOT_UUID}" (reference "{reference}") (unit 1))
\t\t\t)
\t\t)
\t)""")


def add_section(title, x, y):
    texts.append(f"""\t(text "{title}"
\t\t(exclude_from_sim no)
\t\t(at {x:.3f} {y:.3f} 0)
\t\t{effects(2.2, bold=True)}
\t\t(uuid "{uid('text', title)}")
\t)""")


define_symbol(
    "PJ398SM",
    [("T", "TIP", "passive", "left"), ("S", "SLEEVE", "passive", "left"), ("TN", "TIP_NORMAL", "passive", "right")],
    15.24,
    10.16,
)
define_symbol(
    "CONN_2X10",
    [(str(pin), f"PIN_{pin}", "passive", "left" if pin % 2 else "right") for pin in range(1, 21)],
    20.32,
    27.94,
)
define_symbol(
    "CONN_2X12",
    [(str(pin), f"PIN_{pin}", "passive", "left" if pin % 2 else "right") for pin in range(1, 25)],
    20.32,
    33.02,
)


add_section("EIGHT CV OUTPUT JACKS", 20, 18)
for channel in range(1, 9):
    x = 45 + (channel - 1) * 30
    add_component("PJ398SM", f"J{channel}", f"CV OUT {channel}", x, 50, {"T": f"CV_OUT{channel}", "S": "GND"}, PJ398SM_FOOTPRINT)

add_section("EIGHT GATE OUTPUT JACKS", 20, 90)
for channel in range(1, 9):
    x = 45 + (channel - 1) * 30
    add_component("PJ398SM", f"J{channel + 8}", f"GATE OUT {channel}", x, 122, {"T": f"GATE_OUT{channel}", "S": "GND"}, PJ398SM_FOOTPRINT)

add_section("CLOCK AND RESET JACKS", 20, 162)
add_component("PJ398SM", "J17", "CLOCK IN", 55, 194, {"T": "CLOCK_IN_JACK", "S": "GND", "TN": "GND"}, PJ398SM_FOOTPRINT)
add_component("PJ398SM", "J18", "CLOCK OUT", 105, 194, {"T": "CLOCK_OUT_JACK", "S": "GND"}, PJ398SM_FOOTPRINT)
add_component("PJ398SM", "J19", "RESET IN", 155, 194, {"T": "RESET_IN_JACK", "S": "GND", "TN": "GND"}, PJ398SM_FOOTPRINT)

add_section("MAIN BOARD INTERCONNECTS", 220, 162)
cv_panel_nets = {str(channel * 2 - 1): f"CV_OUT{channel}" for channel in range(1, 9)}
cv_panel_nets.update({str(pin): "GND" for pin in range(2, 21, 2)})
add_component("CONN_2X10", "J24", "CV MAIN BOARD", 260, 205, cv_panel_nets, "Connector_IDC:IDC-Header_2x10_P2.54mm_Vertical")

digital_panel_signals = [
    *(f"GATE_OUT{channel}" for channel in range(1, 9)),
    "CLOCK_OUT_JACK",
    "CLOCK_IN_JACK",
    "RESET_IN_JACK",
]
digital_panel_nets = {str(index * 2 - 1): net for index, net in enumerate(digital_panel_signals, 1)}
digital_panel_nets.update({str(pin): "GND" for pin in range(2, 25, 2)})
add_component("CONN_2X12", "J25", "DIGITAL MAIN BOARD", 330, 205, digital_panel_nets, "Connector_IDC:IDC-Header_2x12_P2.54mm_Vertical")


library = "\n".join(symbol_definition(name, symbol) for name, symbol in symbols.items())
external_library = "\n".join(symbol_definition(name, symbol, qualified=False) for name, symbol in symbols.items())
external_library = "\n".join(line[1:] if line.startswith("\t") else line for line in external_library.splitlines())
SYMBOL_LIBRARY_OUTPUT.write_text(f"""(kicad_symbol_lib
\t(version 20231120)
\t(generator "kicad_symbol_editor")
{external_library}
)\n""")
SCHEMATIC_OUTPUT.write_text(f"""(kicad_sch
\t(version 20260306)
\t(generator "eeschema")
\t(generator_version "10.0")
\t(uuid "{ROOT_UUID}")
\t(paper "A3")
\t(title_block
\t\t(title "SEQ-08 Passive PJ398SM Jack Board")
\t\t(date "2026-07-17")
\t\t(rev "A")
\t\t(company "SEQ-08")
\t\t(comment 1 "Eight CV, eight gate, clock input/output, and reset input jacks")
\t\t(comment 2 "No active circuitry, connected to the main PCB with keyed IDC cables")
\t)
\t(lib_symbols
{library}
\t)
{chr(10).join(no_connects)}
{chr(10).join(labels)}
{chr(10).join(texts)}
{chr(10).join(components)}
\t(sheet_instances
\t\t(path "/" (page "1"))
\t)
)\n""")
